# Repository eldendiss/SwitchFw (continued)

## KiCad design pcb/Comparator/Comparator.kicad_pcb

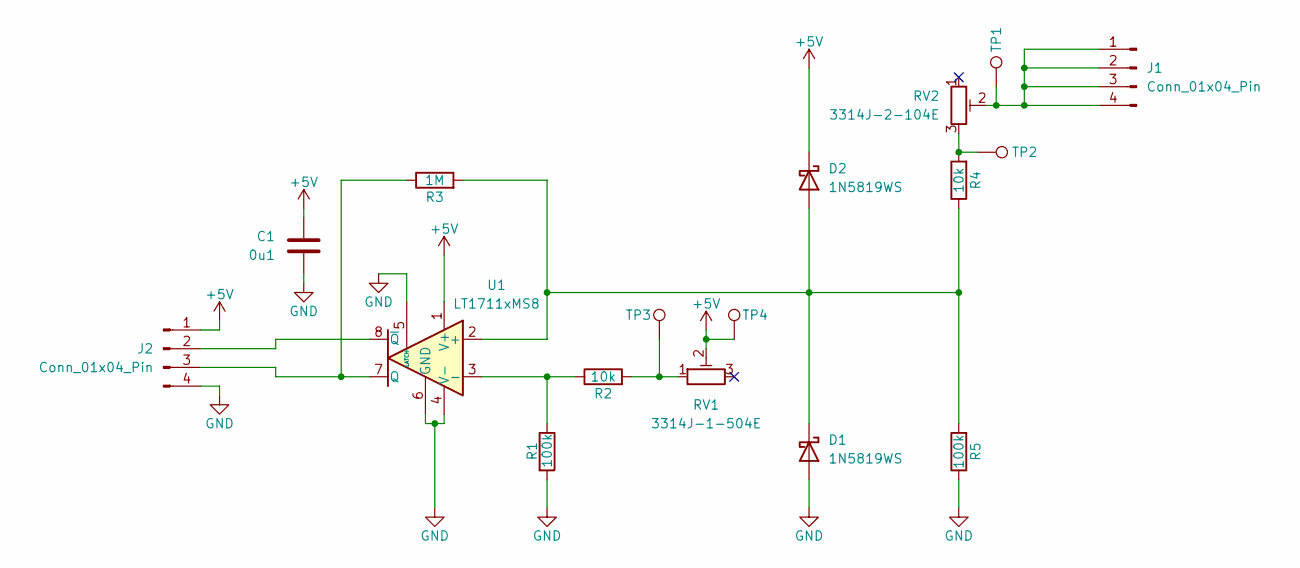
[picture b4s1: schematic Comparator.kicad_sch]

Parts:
C1: 0u1; C_0603_1608Metric
D1, D2: 1N5819WS; D_SOD-323
J1, J2: Conn_01x04_Pin; PinHeader_1x04_P2.54mm_Vertical
R1, R5: 100k; R_0603_1608Metric
R2, R4: 10k; R_0603_1608Metric
R3: 1M; R_0603_1608Metric
RV1: 3314J-1-504E; Potentiometer_Bourns_3314J_Vertical
RV2: 3314J-2-104E; Potentiometer_Bourns_3314J_Vertical
TP1, TP2, TP3, TP4: TestPoint; TestPoint_Pad_D1.5mm
U1: LT1711xMS8; MSOP-8_3x3mm_P0.65mm

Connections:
+5V: C1.1, D2.1 (K), J2.1, RV1.2, TP4.1, U1.1 (V+)
GND: C1.2, D1.2 (A), J2.4, R1.2, R5.1, U1.4 (V-), U1.5 (LATCH), U1.6 (GND)
unnamed: D1.1 (K), D2.2 (A), R3.2, R4.1, R5.2, U1.2 (+)
unnamed: J1.1, J1.2, J1.3, J1.4, RV2.2, TP1.1
unnamed: J2.2, U1.8 (~Q)
unnamed: J2.3, R3.1, U1.7 (Q)
unnamed: R2.2, RV1.1, TP3.1
unnamed: R4.2, RV2.3, TP2.1
unnamed: R1.1, R2.1, U1.3 (-)

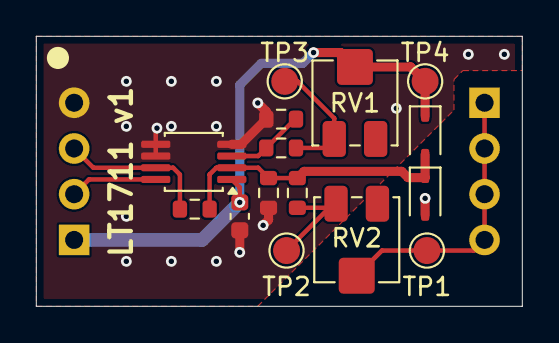
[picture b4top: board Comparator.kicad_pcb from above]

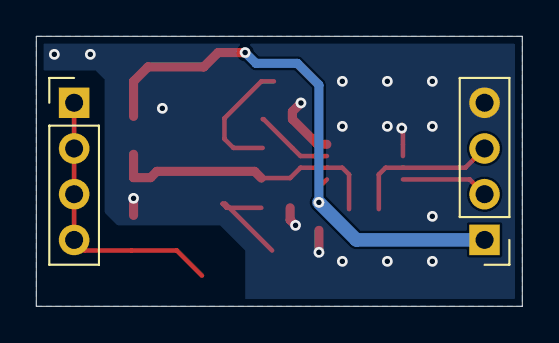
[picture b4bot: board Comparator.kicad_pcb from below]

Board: 2 copper layers, 27.0 x 15.0 mm, 17 parts (2 on the bottom side), 9 nets.

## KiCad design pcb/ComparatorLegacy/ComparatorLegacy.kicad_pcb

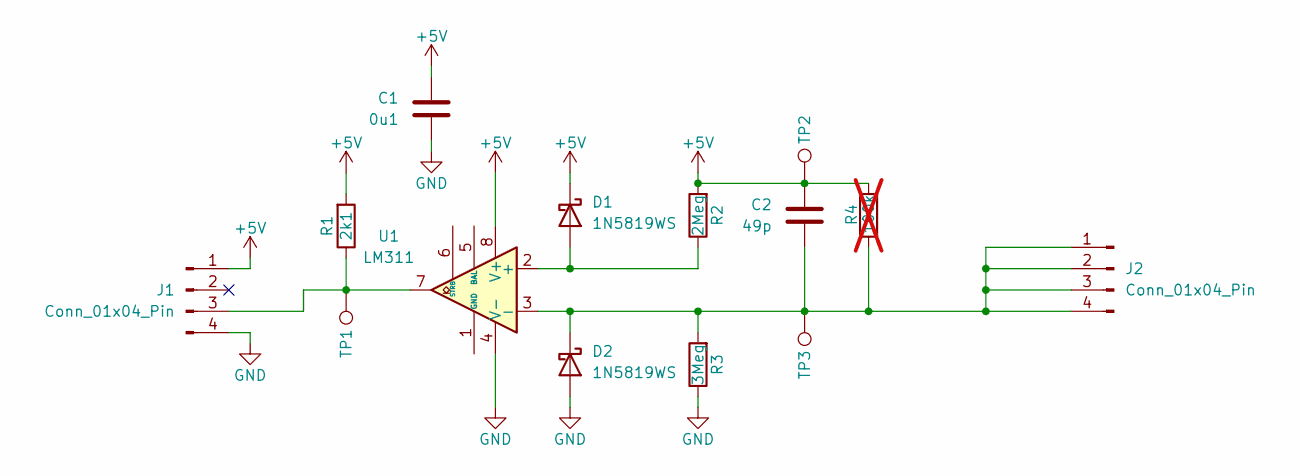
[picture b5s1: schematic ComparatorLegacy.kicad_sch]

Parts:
C1: 0u1; C_0603_1608Metric
C2: 49p; C_0603_1608Metric
D1, D2: 1N5819WS; D_SOD-323
J1, J2: Conn_01x04_Pin; PinHeader_1x04_P2.54mm_Vertical
R1: 2k1; R_0603_1608Metric
R2: 2Meg; R_0603_1608Metric
R3: 3Meg; R_0603_1608Metric
R4: 100k; R_0603_1608Metric; not fitted
TP1, TP2, TP3: TestPoint; TestPoint_Pad_D1.5mm
U1: LM311; DIP-8_W7.62mm

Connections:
+5V: C1.1, C2.1, D1.1 (K), J1.1, R1.2, R2.2, R4.1, TP2.1, U1.8 (V+)
GND: C1.2, D2.2 (A), J1.4, R3.1, U1.4 (V-)
unnamed: D1.2 (A), R2.1, U1.2 (+)
unnamed: C2.2, D2.1 (K), J2.1, J2.2, J2.3, J2.4, R3.2, R4.2, TP3.1, U1.3 (-)
unnamed: J1.3, R1.1, TP1.1, U1.7

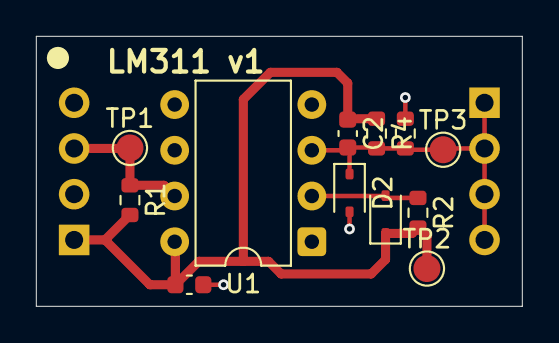
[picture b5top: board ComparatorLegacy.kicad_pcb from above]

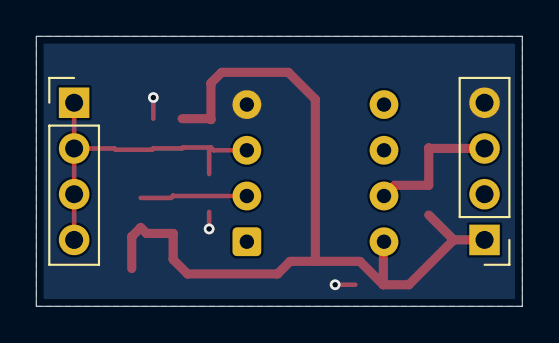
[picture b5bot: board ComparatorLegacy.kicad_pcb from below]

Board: 2 copper layers, 27.0 x 15.0 mm, 14 parts (2 on the bottom side), 5 nets.

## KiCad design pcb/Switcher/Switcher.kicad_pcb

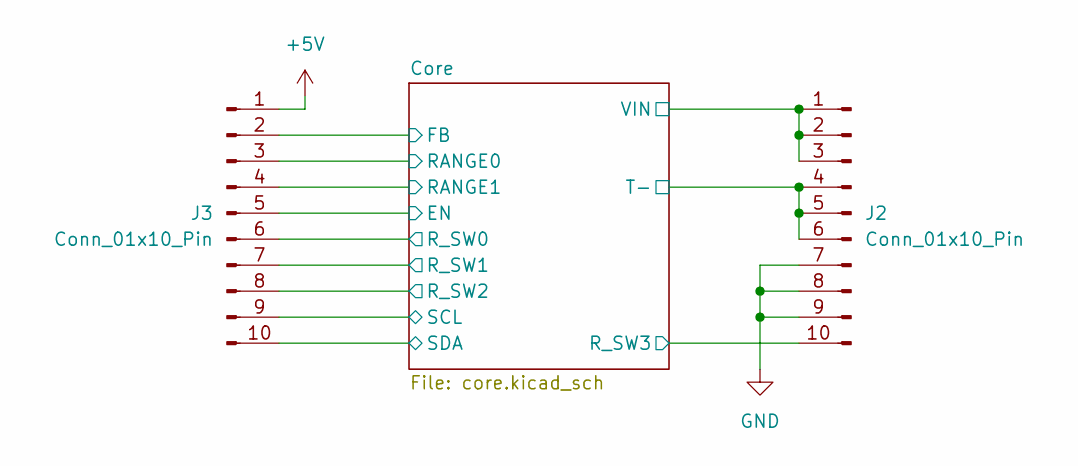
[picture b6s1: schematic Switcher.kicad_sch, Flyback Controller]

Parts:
J2, J3: Conn_01x10_Pin; PinHeader_1x10_P2.54mm_Vertical

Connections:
+5V: J3.1; also elsewhere on the board
/Core/EN: J3.5; also elsewhere on the board
/Core/FB: J3.2; also elsewhere on the board
/Core/RANGE0: J3.3; also elsewhere on the board
/Core/RANGE1: J3.4; also elsewhere on the board
/Core/R_SW0: J3.6; also elsewhere on the board
/Core/R_SW1: J3.7; also elsewhere on the board
/Core/R_SW2: J3.8; also elsewhere on the board
/Core/R_SW3: J2.10; also elsewhere on the board
/Core/SCL: J3.9; also elsewhere on the board
/Core/SDA: J3.10; also elsewhere on the board
/Core/T-: J2.4, J2.5, J2.6; also elsewhere on the board
/Core/VIN: J2.1, J2.2, J2.3; also elsewhere on the board
GND: J2.7, J2.8, J2.9; also elsewhere on the board

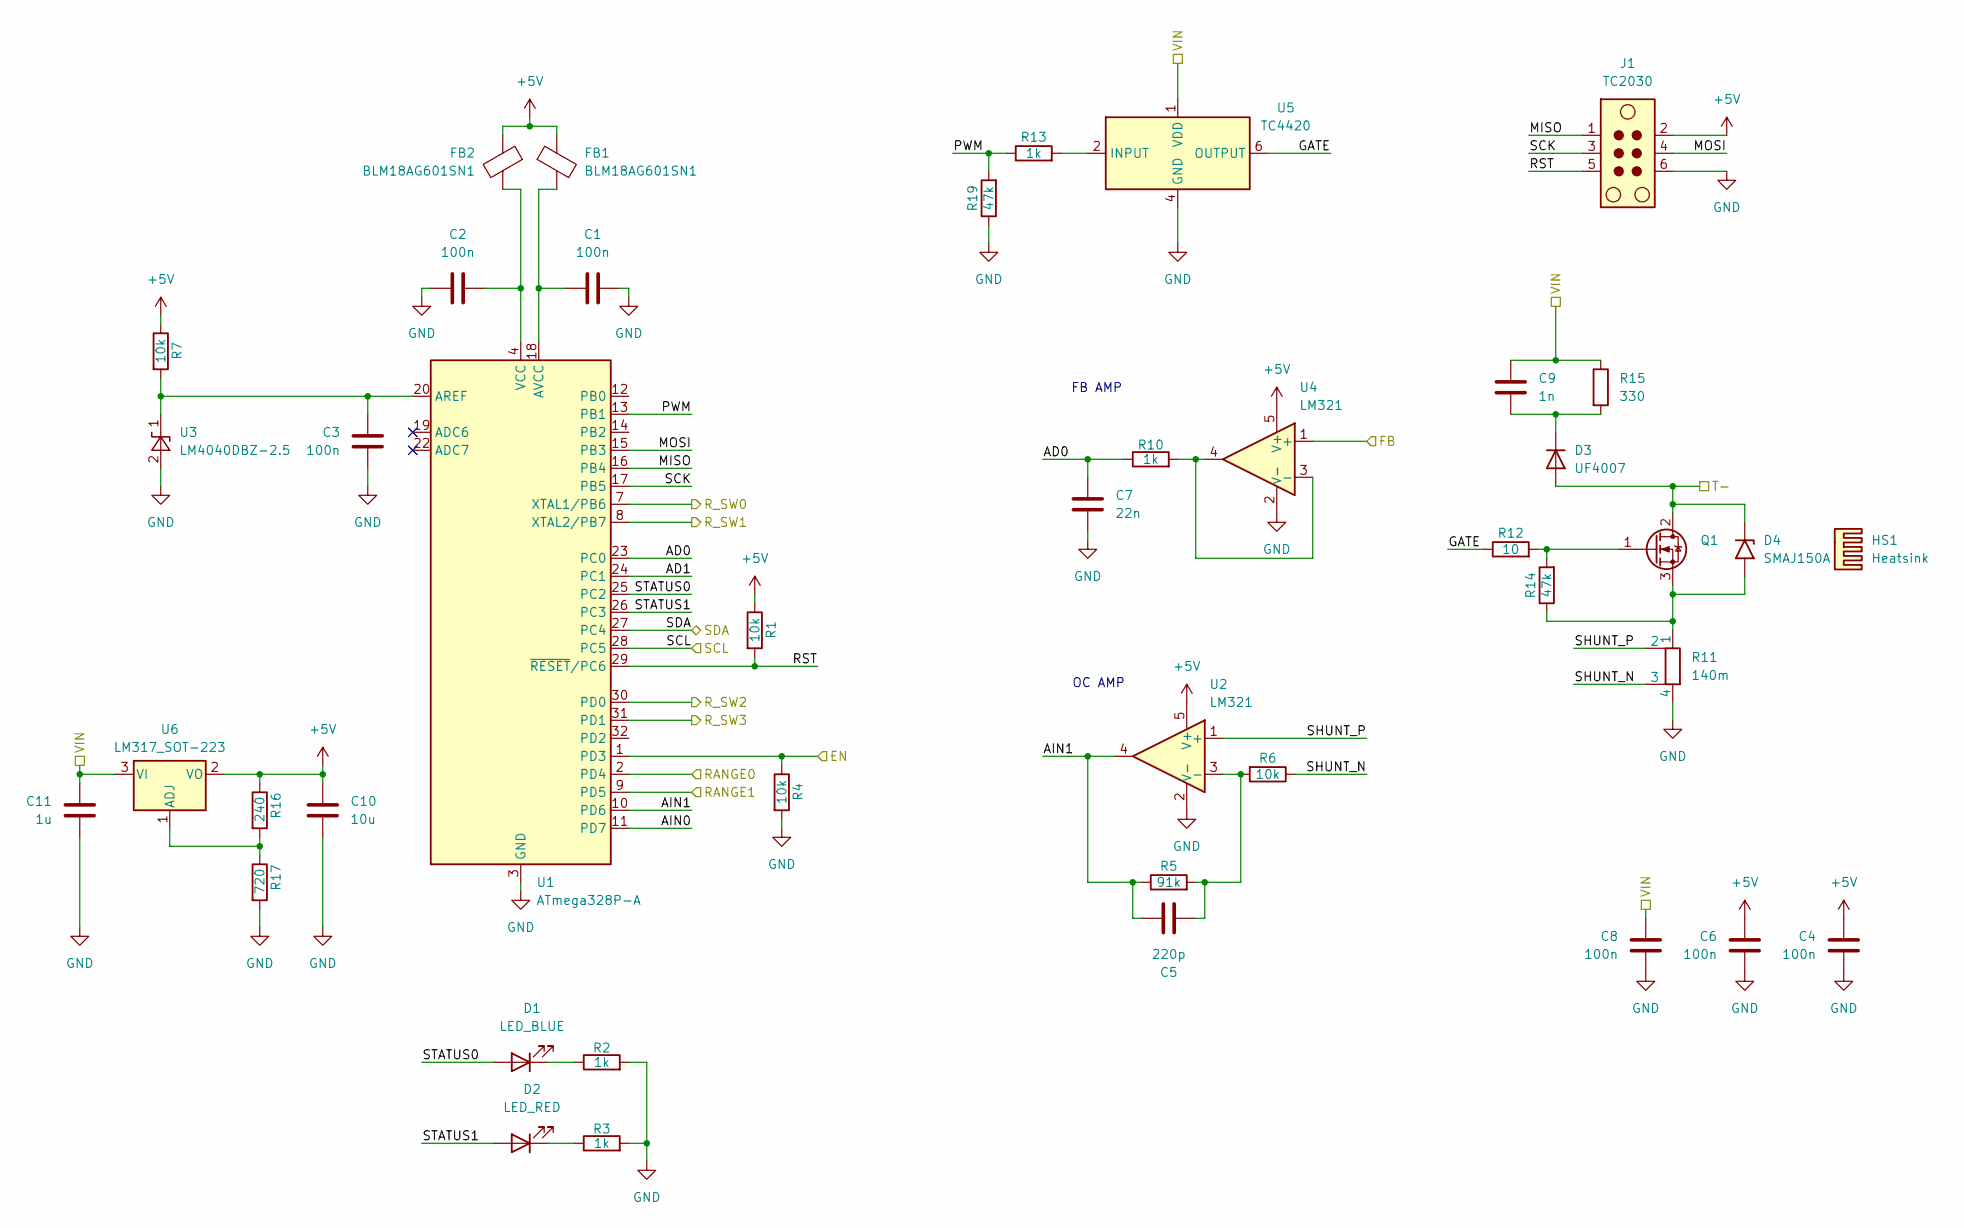
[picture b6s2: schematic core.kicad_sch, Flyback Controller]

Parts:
C1, C2, C3, C4, C6, C8: 100n; C_0603_1608Metric
C5: 220p; C_0603_1608Metric
C7: 22n; C_0603_1608Metric
C9: 1n; C_1206_3216Metric
C10: 10u; C_1206_3216Metric
C11: 1u; C_0603_1608Metric
D1: LED_BLUE; LED_0603_1608Metric
D2: LED_RED; LED_0603_1608Metric
D3: UF4007; D_DO-41_SOD81_P10.16mm_Horizontal
D4: SMAJ150A; D_SMA
FB1, FB2: BLM18AG601SN1; L_0603_1608Metric
HS1: Heatsink; Heatsink_Stonecold_HS-S01_13.21x6.35mm
J1: TC2030; Tag-Connect_TC2030-IDC-NL_2x03_P1.27mm_Vertical
Q1: IPP075N15N3; TO-220-3_Vertical
R1, R4, R6, R7: 10k; R_0603_1608Metric
R2, R3, R10, R13: 1k; R_0603_1608Metric
R5: 91k; R_0603_1608Metric
R11: 140m; R_Shunt_Vishay_WSK2512_6332Metric_T2.21mm
R12: 10; R_0603_1608Metric
R14, R19: 47k; R_0603_1608Metric
R15: 330; R_2512_6332Metric
R16: 240; R_0603_1608Metric
R17: 720; R_0603_1608Metric
U1: ATmega328P-A; TQFP-32_7x7mm_P0.8mm
U2, U4: LM321; SOT-23-5
U3: LM4040DBZ-2.5; SOT-23
U5: TC4420; SOIC-8_3.9x4.9mm_P1.27mm
U6: LM317_SOT-223; SOT-223-3_TabPin2

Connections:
+5V: C4.2, C6.2, C10.2, FB1.1, FB2.1, J1.2, R1.1, R7.1, R16.1, U2.5 (V+), U4.5 (V+), U6.2 (VO); also elsewhere on the board
/Core/AD0: C7.2, R10.1, U1.23 (PC0)
/Core/AD1: U1.24 (PC1)
/Core/AIN0: U1.11 (PD7)
/Core/AIN1: C5.1, R5.1, U1.10 (PD6), U2.4
/Core/EN: R4.1, U1.1 (PD3); also elsewhere on the board
/Core/FB: U4.1 (+); also elsewhere on the board
/Core/GATE: R12.1, U5.6 (OUTPUT), U5.7 (OUTPUT)
/Core/MISO: J1.1, U1.16 (PB4)
/Core/MOSI: J1.4, U1.15 (PB3)
/Core/PWM: R13.1, R19.2, U1.13 (PB1)
/Core/RANGE0: U1.2 (PD4); also elsewhere on the board
/Core/RANGE1: U1.9 (PD5); also elsewhere on the board
/Core/RST: J1.5, R1.2, U1.29 (~RESET/PC6)
/Core/R_SW0: U1.7 (XTAL1/PB6); also elsewhere on the board
/Core/R_SW1: U1.8 (XTAL2/PB7); also elsewhere on the board
/Core/R_SW2: U1.30 (PD0); also elsewhere on the board
/Core/R_SW3: U1.31 (PD1); also elsewhere on the board
/Core/SCK: J1.3, U1.17 (PB5)
/Core/SCL: U1.28 (PC5); also elsewhere on the board
/Core/SDA: U1.27 (PC4); also elsewhere on the board
/Core/SHUNT_N: R6.1, R11.3
/Core/SHUNT_P: R11.2, U2.1 (+)
/Core/STATUS0: D1.2 (A), U1.25 (PC2)
/Core/STATUS1: D2.2 (A), U1.26 (PC3)
/Core/T-: D3.2 (A), D4.1 (A1), Q1.2 (D); also elsewhere on the board
/Core/VIN: C8.2, C9.2, C11.1, R15.1, U5.1 (VDD), U5.8 (VDD), U6.3 (VI); also elsewhere on the board
GND: C1.2, C2.2, C3.2, C4.1, C6.1, C7.1, C8.1, C10.1, C11.2, J1.6, R2.2, R3.2, R4.2, R11.4, R17.2, R19.1, U1.3 (GND), U1.5 (GND), U1.21 (GND), U2.2 (V-), U3.2 (A), U4.2 (V-), U5.4 (GND), U5.5 (GND); also elsewhere on the board
unnamed: C2.1, FB2.2, U1.4 (VCC), U1.6 (VCC)
unnamed: D1.1 (K), R2.1
unnamed: D2.1 (K), R3.1
unnamed: C9.1, D3.1 (K), R15.2
unnamed: D4.2 (A2), Q1.3 (S), R11.1, R14.1
unnamed: Q1.1 (G), R12.2, R14.2
unnamed: C3.1, R7.2, U1.20 (AREF), U3.1 (K)
unnamed: C1.1, FB1.2, U1.18 (AVCC)
unnamed: C5.2, R5.2, R6.2, U2.3 (-)
unnamed: R10.2, U4.3 (-), U4.4
unnamed: R13.2, U5.2 (INPUT)
unnamed: R16.2, R17.1, U6.1 (ADJ)

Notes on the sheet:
OC AMP
FB AMP

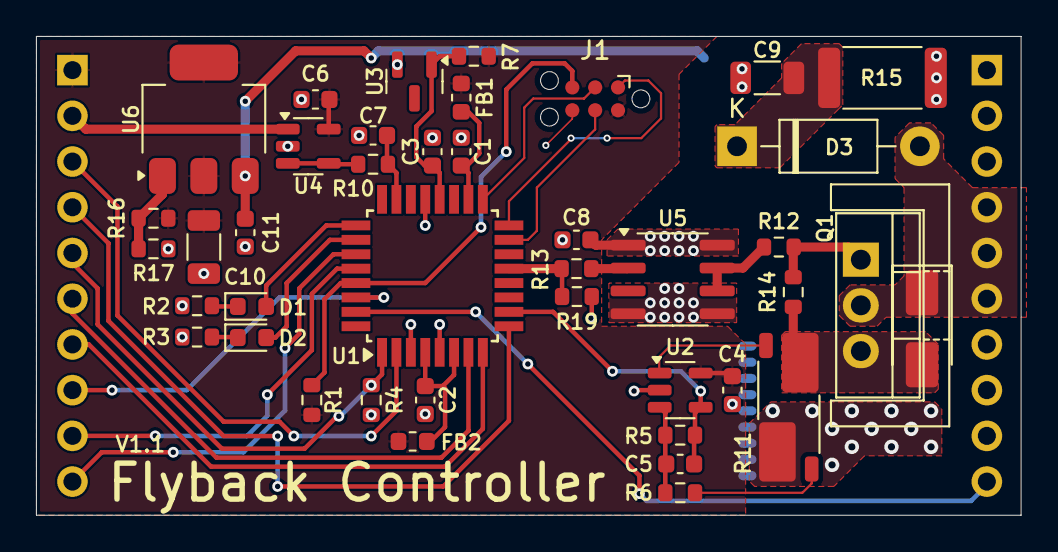
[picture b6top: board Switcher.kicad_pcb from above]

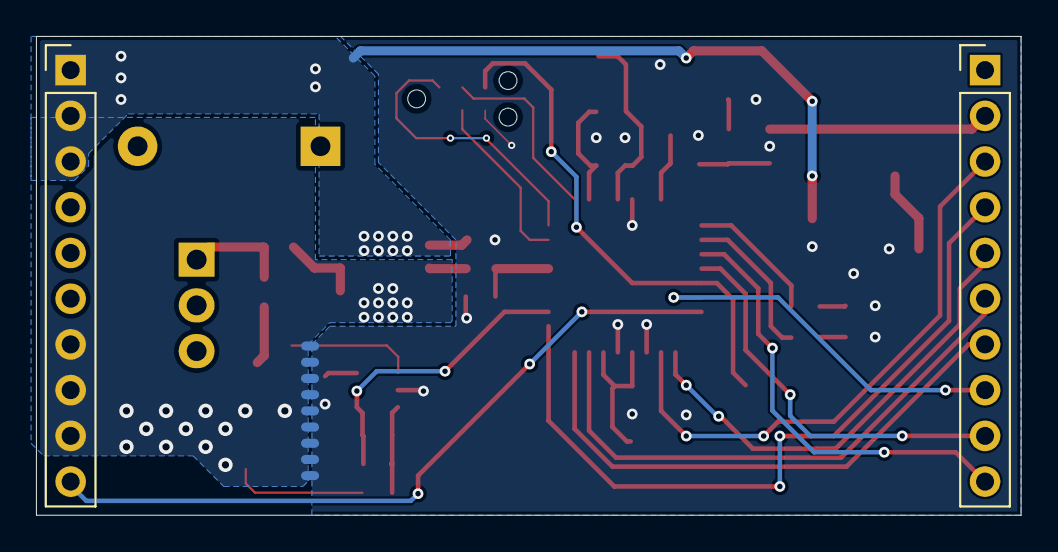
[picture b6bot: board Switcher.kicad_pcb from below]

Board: 2 copper layers, 54.7 x 26.6 mm, 44 parts (2 on the bottom side), 38 nets.

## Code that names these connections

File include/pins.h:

#pragma once
#include <Arduino.h>

/**
 * \file
 * \brief Direct I/O helpers and pin map (AVR bit indices, not Arduino pin numbers).
 * \details
 * Defines port bit positions for a flyback/PSU board and provides small inline helpers:
 * - LED control on PC2/PC3
 * - External EN input on PD3
 * - 2-bit range code read on PD4/PD5 (active-low)
 * - Resistor-switch controls on PB6/PB7/PD0/PD1
 *
 * \note All pin macros below are **bit numbers** (e.g., \c PD4 == 4) to be used with
 * DDRx/PORTx/PINx and \c _BV(). They are **not** Arduino digital pin IDs.
 *
 * PD4 and PD5 are free — connected to ESP32 for future use (no pull-ups configured).
 */

// --- User pin assignments (bits, not Arduino numbers) ---

/** \brief Gate drive output (bit index on PORTB). */
#define GATE_OUT PB1
/** \brief Feedback input (bit index on PORTC). Typically analog/ADC node. */
#define FB_IN PC0

/** \brief Over-current / analog comparator input (AIN0) on PORTD. */
#define OC_IN PD6 // AIN0 (comparator input)
/** \brief External enable input on PORTD (see EN helpers below). */
#define EN_IN PD3

// PD4 and PD5 are free — connected directly to ESP32 for future use.

/** \brief Green OK LED on PORTC bit 2. */
#define LED_OK PC2
/** \brief Red FAULT LED on PORTC bit 3. */
#define LED_FAULT PC3

/** \brief Resistor-switch output 0 (divider control) on PORTB. */
#define R_SW0 PB6
/** \brief Resistor-switch output 1 on PORTB. */
#define R_SW1 PB7
/** \brief Resistor-switch output 2 on PORTD. */
#define R_SW2 PD0
/** \brief Resistor-switch output 3 on PORTD. */
#define R_SW3 PD1

// --- Port helpers (direct I/O) ---

/**
 * \brief 8-bit variant of \c _BV() for clarity with uint8_t expressions.
 * \param b Bit position (0..7).
 * \return (uint8_t)1U << b
 */
#define _BV8(b) (uint8_t(1U) << (b))

// -----------------------------------------------------------------------------
// LEDs
// -----------------------------------------------------------------------------

/**
 * \brief Drive the OK LED on PC2.
 * \param on \c true turns the LED on (if wired active-high), \c false turns it off.
 * \note Assumes DDRC for PC2 was configured as output elsewhere.
 */
static inline void led_ok_set(bool on)
{
  if (on)
    PORTC |= _BV8(LED_OK);
  else
    PORTC &= ~_BV8(LED_OK);
}

/**
 * \brief Drive the FAULT LED on PC3.
 * \param on \c true turns the LED on (if wired active-high), \c false turns it off.
 * \note Assumes DDRC for PC3 was configured as output elsewhere.
 */
static inline void led_fault_set(bool on)
{
  if (on)
    PORTC |= _BV8(LED_FAULT);
  else
    PORTC &= ~_BV8(LED_FAULT);
}

// -----------------------------------------------------------------------------
// EN (active-low external input on PD3)
// -----------------------------------------------------------------------------

/**
 * \brief Configure PD3 as a plain input for external EN (no internal pull-up).
 * \details
 * - Sets DDRD.PD3 = 0 (input) and clears PORTD.PD3 (disables pull-up).
 * - Clears TCCR2A.COM2B[1:0] to ensure Timer2 isn't driving OC2B on PD3.
 */
static inline void EN_init_input()
{
  // Input, NO internal pull-up (external pulldown).
  DDRD &= ~_BV(PD3);
  PORTD &= ~_BV(PD3); // ensure pull-up is OFF
  // Make sure Timer2 isn't driving OC2B on PD3
  TCCR2A &= ~(_BV(COM2B1) | _BV(COM2B0));
}

/**
 * \brief Read the EN input level.
 * \return \c true if PD3 is high, \c false if low.
 * \note EN is active-high, \c false means "disabled".
 */
static inline bool EN_is_active() { return (PIND & _BV(PD3)) != 0; }

// -----------------------------------------------------------------------------
// Resistor-divider switches (outputs)
// -----------------------------------------------------------------------------

/**
 * \brief Initialize R_SW pins as outputs (state unchanged).
 * \details Sets DDRB bits for PB6/PB7 and DDRD bits for PD0/PD1.
 * \note Call rsw_all_open() after init if you need a defined low/off state.
 */
static inline void rsw_init()
{
  DDRB |= _BV8(R_SW0) | _BV8(R_SW1);
  DDRD |= _BV8(R_SW2) | _BV8(R_SW3);
}

/**
 * \brief Open all resistor-switches (drive control lines low).
 * \details Clears PORTB bits PB6/PB7 and PORTD bits PD0/PD1.
 * \note Adjust if your hardware uses opposite polarity.
 */
static inline void rsw_all_open()
{
  PORTB &= ~(_BV8(R_SW0) | _BV8(R_SW1));
  PORTD &= ~(_BV8(R_SW2) | _BV8(R_SW3));
}

/**
 * \brief Close exactly one resistor-switch according to a 2-bit code.
 * \param code Lower 2 bits select which switch: 0→PB6, 1→PB7, 2→PD0, 3→PD1.
 * \details Clears all switches via rsw_all_open(), then sets the selected one.
 * \warning Verify mapping vs. PCB; change the switch/case if wiring differs.
 */
static inline void rsw_make(uint8_t code)
{
  // 0..3 maps to one of the four switches. Adjust mapping to your HW.
  rsw_all_open();
  switch (code & 3)
  {
  case 0:
    PORTB |= _BV8(R_SW0);
    break;
  case 1:
    PORTB |= _BV8(R_SW1);
    break;
  case 2:
    PORTD |= _BV8(R_SW2);
    break;
  case 3:
    PORTD |= _BV8(R_SW3);
    break;
  }
}

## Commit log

2025-08-16 Working version 1
2025-08-17 Working PWM
2025-09-12 working v0.9
2025-09-12 Update LED signaling
2025-09-15 Working
2025-09-15 Add PFM
2025-09-15 Add docu and auto range selector and geiger counter
2025-09-15 Add readme
2025-09-16 Update readmes, licenses
2025-12-02 Add example
2025-12-09 Update pins
2025-12-14 Add pcb
2025-12-22 Ongoing
2025-12-24 Base version
2025-12-24 Working version
2025-12-25 Separate CPM for each channel Fix storage Enable commands from iSDG
2025-12-28 Add BLE
2025-12-28 Dev ra sens (#4)
    * Ongoing
    * Base version
    * Working version
    * Separate CPM for each channel
    Fix storage
    Enable commands from iSDG
2026-01-12 TLDR
2026-03-01 Add range reporting
2026-03-19 Add separate tags for ranges
2026-03-20 Bump IoT_IS
2026-03-25 Add dose rate
2026-03-25 Reduce filtering
2026-03-26 v1.0.8
2026-04-01 Update PCNT filter to 500ns
2026-04-19 V5 version
2026-04-19 Disable flyback on boot for safety
2026-04-23 Fix bootloop when wifi is not present
2026-04-23 Fix MQTT related bugs
2026-04-23 Fix job bugs, add IF sensor
2026-04-27 remove LAN bootloop
2026-04-27 Bugfixes
2026-05-06 Hardening
2026-05-10 Reduce consumption, try to fix OTA
2026-05-10 Add ADC battery sampling
2026-05-18 Try to fix long-running hangs
2026-05-21 PCB 485
